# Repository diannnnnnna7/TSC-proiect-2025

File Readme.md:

E-Book Reader cu e-Paper si ESP32-C6

DeskAssistant este un dispozitiv portabil de tip E-Book Reader, construit in jurul microcontrolerului ESP32-C6, cu consum redus de energie si capabilitati de conectivitate Wi-Fi. Dispozitivul utilizeaza un display e-paper pentru citirea confortabila a cartilor, fiind alimentat de la o baterie Li-Po si gandit sa functioneze autonom timp indelungat.

Componente principale:

ESP32-C6 – Microcontroler principal cu Wi-Fi, SPI si I2C

E-Paper Display – Afisaj principal, ideal pentru citirea fara oboseala a ochilor

Memorie Flash NOR 64MB – Spatiu generos pentru carti, configurari sau fisiere

Senzor ambiental BME688 – Masoara temperatura, presiunea, umiditatea si calitatea aerului

RTC DS3231 – Ceas de timp real cu precizie ridicata si consum scazut

SD Card Slot – Optiune de stocare suplimentara pentru fisiere EPUB/PDF

Fuel Gauge MAX17048 – Monitorizeaza in timp real nivelul bateriei

LDO Regulator – Asigura tensiunea de 3.3V stabila pentru toate componentele

Conector USB-C – Incarcare si comunicatie UART pentru debugging

Dispozitivul se alimenteaza de la o baterie Li-Po si poate fi incarcat prin portul USB-C, avand un circuit de incarcare dedicat (MCP73831).

Interfete de comunicatie:

SPI – Utilizat pentru E-Paper, memorie Flash si card SD

I2C – Utilizat pentru senzorul BME688, RTC si Fuel Gauge

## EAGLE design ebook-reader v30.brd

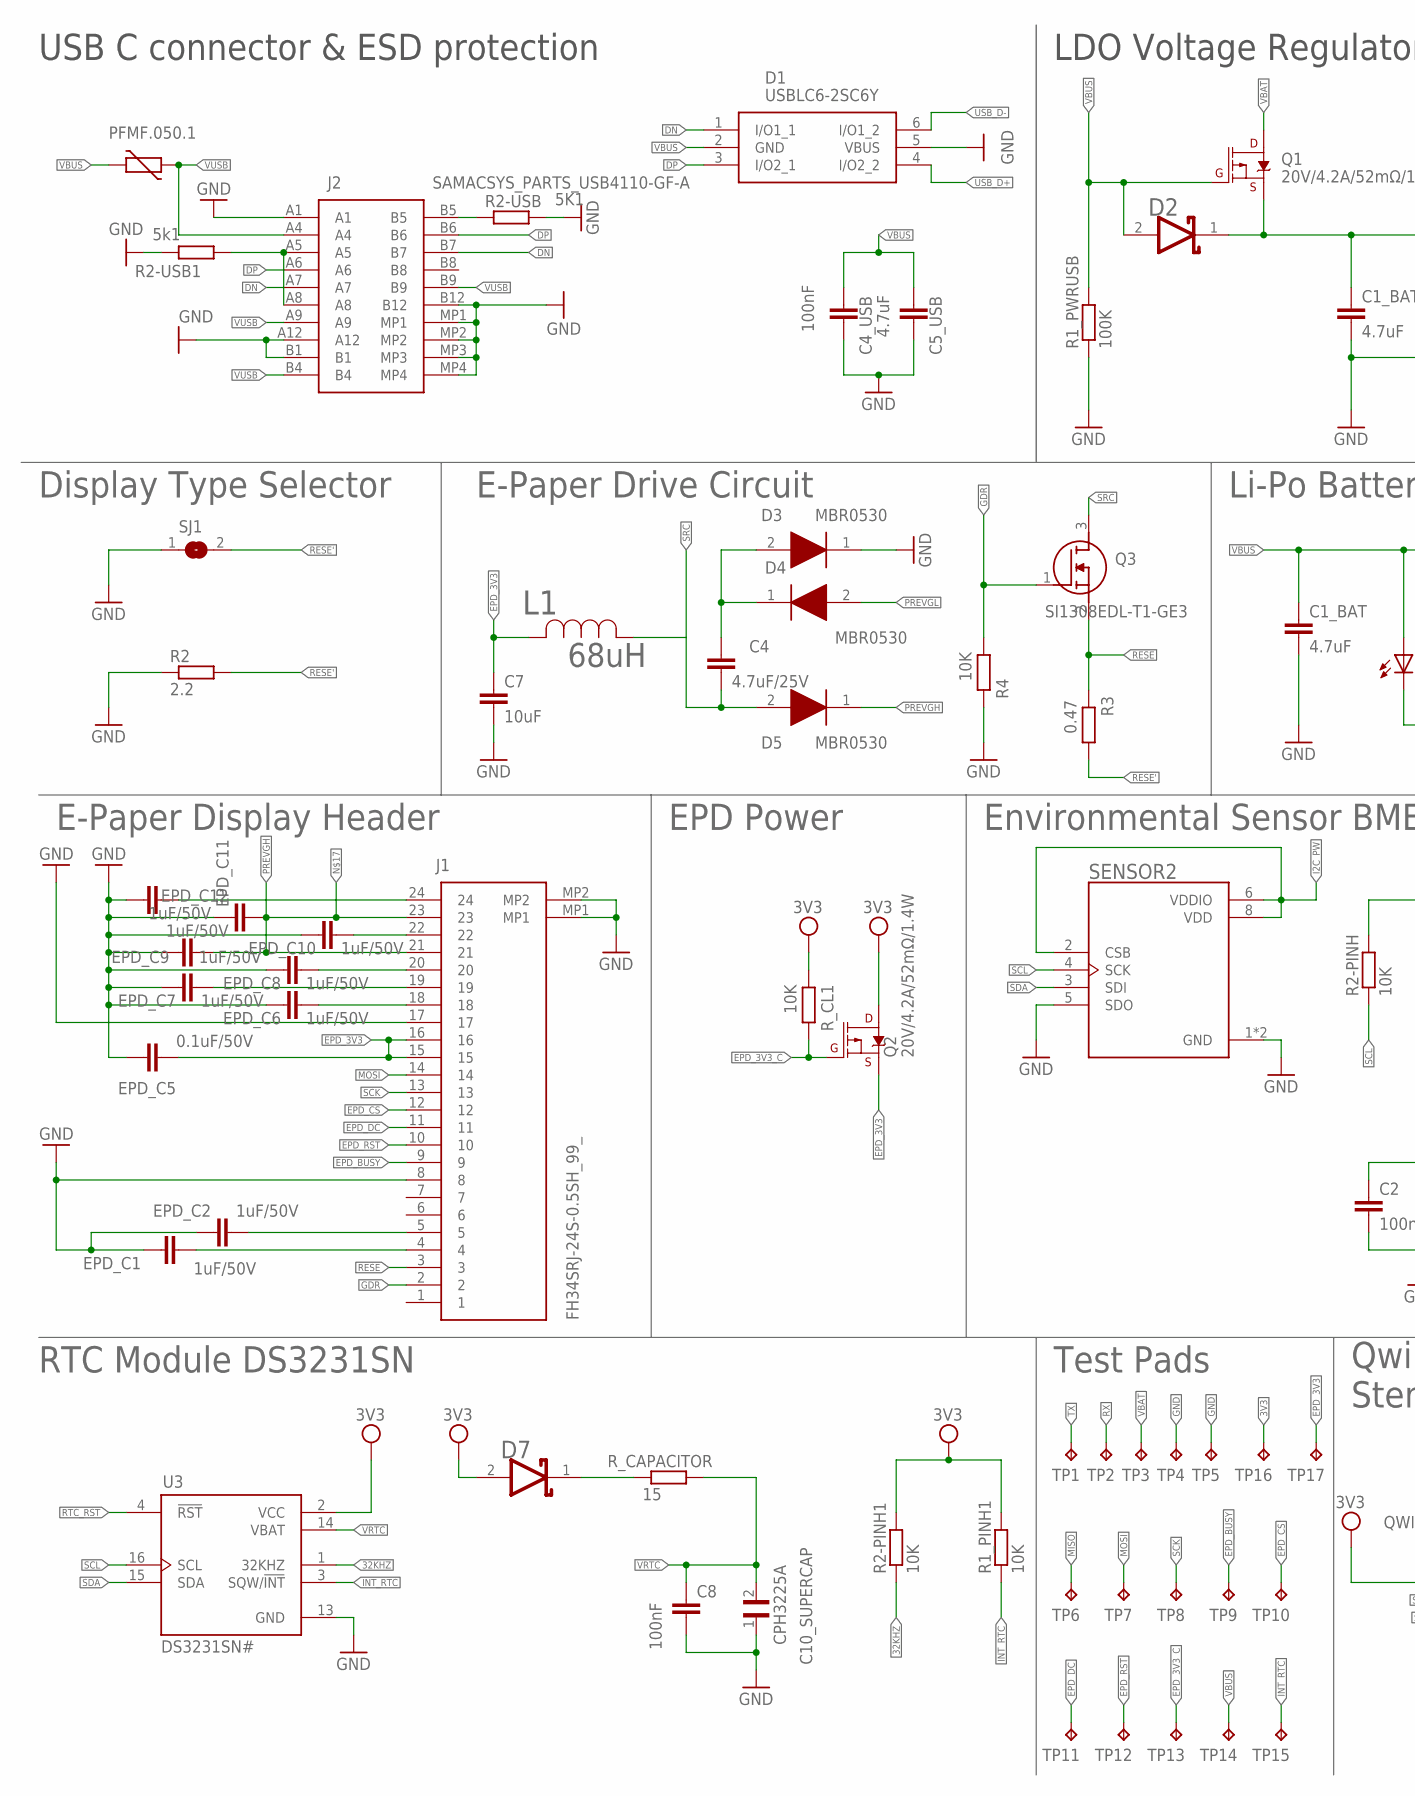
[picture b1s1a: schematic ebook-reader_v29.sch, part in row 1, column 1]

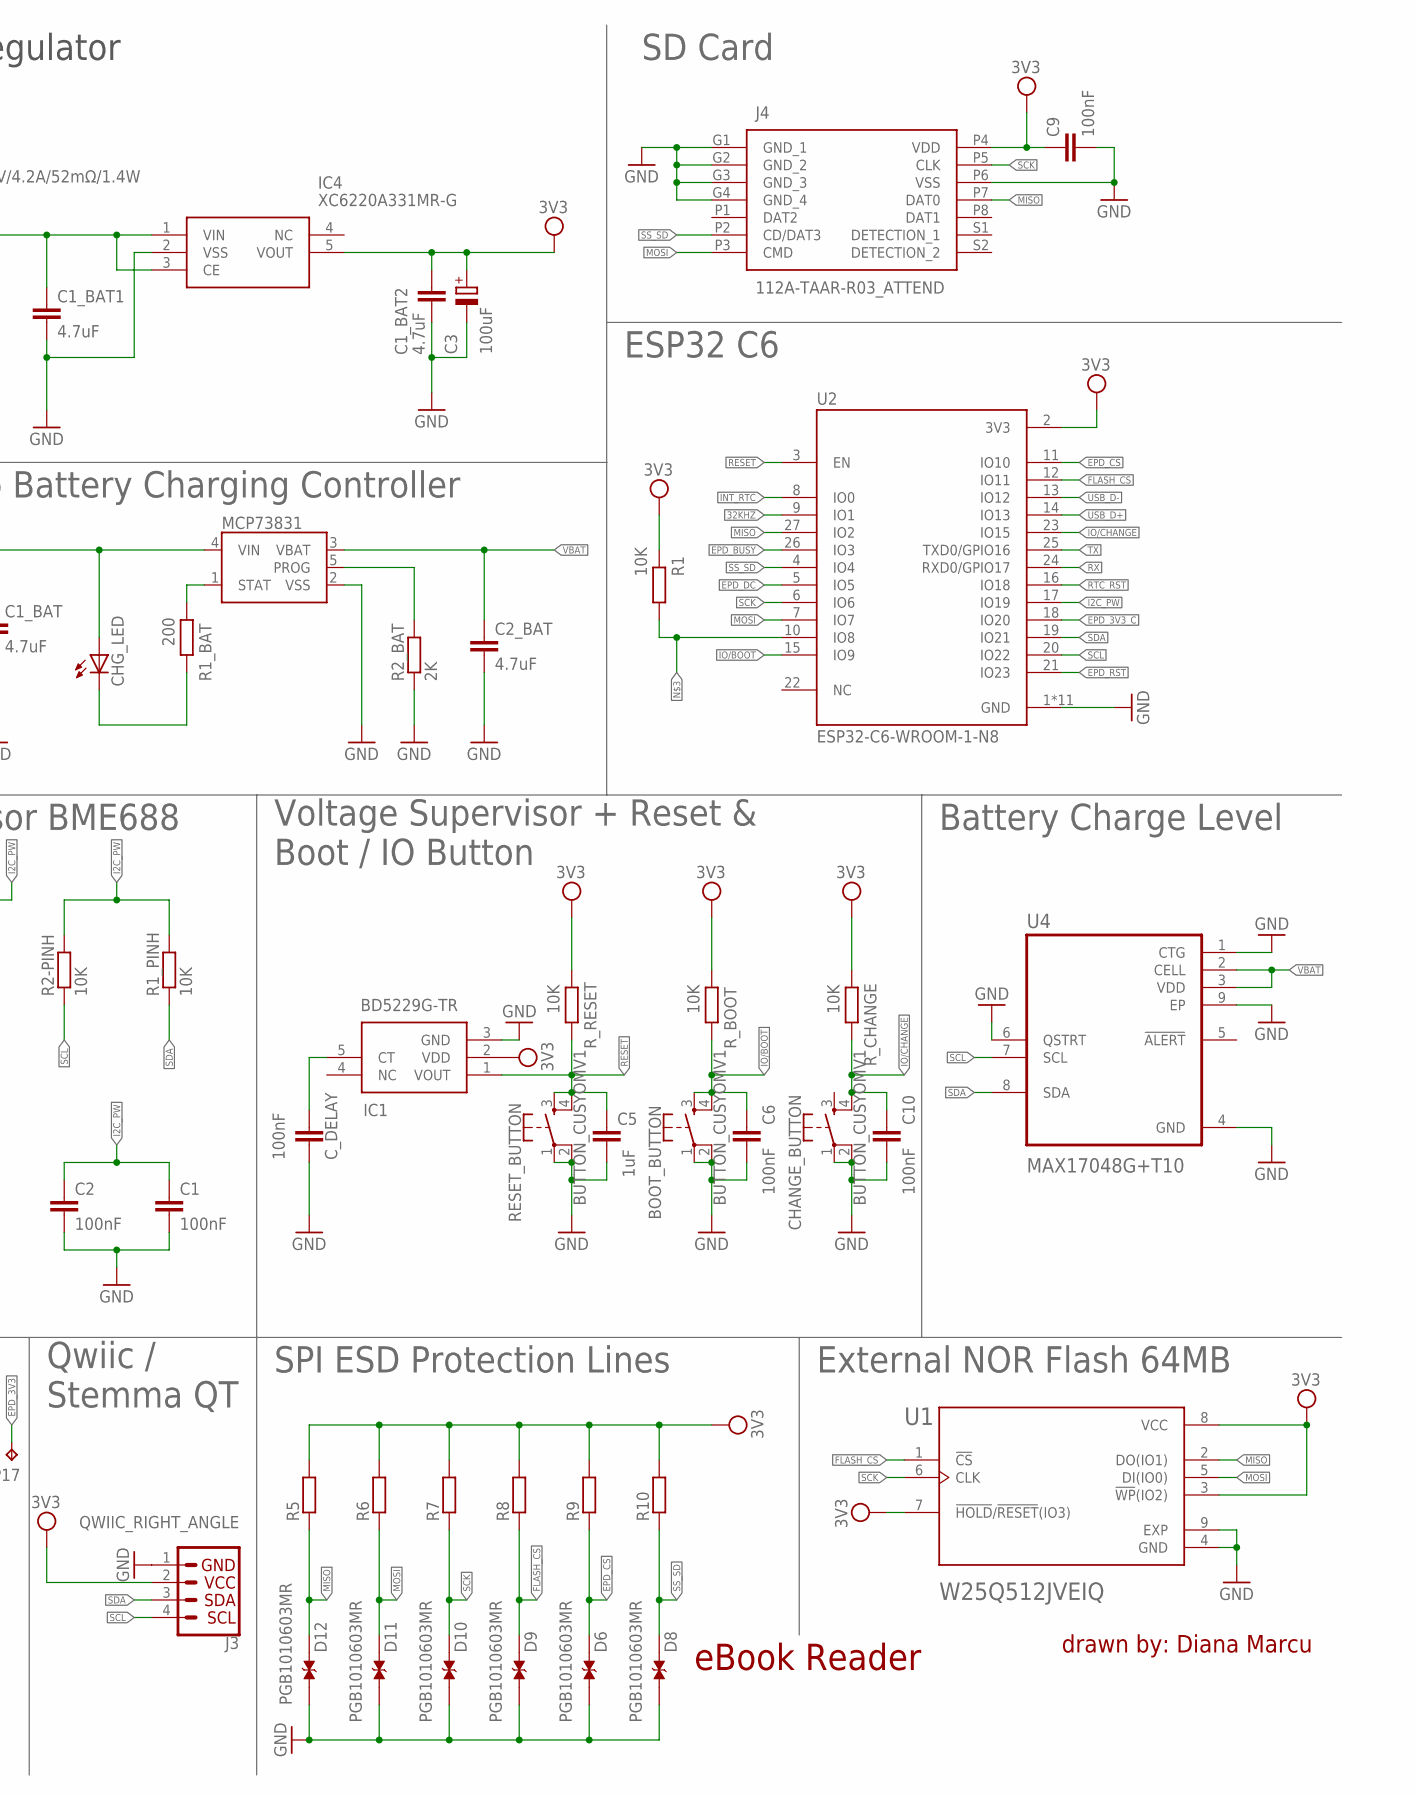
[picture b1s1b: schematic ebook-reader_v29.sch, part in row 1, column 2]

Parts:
BOOT_BUTTON: BUTTON_CUSYOMV1; MYBUTTON
C1, C2, C4_USB, C6, C8, C9, C10: 100nF; EAGLE-LTSPICE_C0402
C1_BAT, C1_BAT1, C1_BAT2, C2_BAT, C5_USB: 4.7uF; EAGLE-LTSPICE_C0402
C3: 100uF; RCL_CT3528
C4: 4.7uF/25V; EAGLE-LTSPICE_C0402
C5: 1uF; EAGLE-LTSPICE_C0402
C7: 10uF; EAGLE-LTSPICE_C0402
C10_SUPERCAP: CPH3225A; CAPCP3225X100N
CHANGE_BUTTON: BUTTON_CUSYOMV1; MYBUTTON
CHG_LED: ADAFRUIT_LEDCHIP-LED0603; ADAFRUIT_CHIP-LED0603
C_DELAY: 100nF; EAGLE-LTSPICE_C0402
D1: USBLC6-2SC6Y; SOT95P280X145-6N
D2, D7: ESP32_WROVER_AVX---SD0805S020S1R0_AVX_SD0805S020S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; ESP32_WROVER_AVX---SD0805S020S1R0_AVX_SD0805S020S1R0_0
D3, D4, D5: MBR0530; SOD3716X135N
D6, D8, D9, D10, D11, D12: PGB1010603MR; DIOC1608X36N
EPD_C1, EPD_C2, EPD_C6, EPD_C7, EPD_C8, EPD_C9, EPD_C10, EPD_C11, EPD_C12: 1uF/50V; EAGLE-LTSPICE_C0402
EPD_C5: 0.1uF/50V; EAGLE-LTSPICE_C0402
IC1: BD5229G-TR; SOT95P280X125-5N
IC4: XC6220A331MR-G; SOT95P280X120-5N
J1: FH34SRJ-24S-0.5SH_99_; FH34SRJ24S05SH99
J2: SAMACSYS_PARTS_USB4110-GF-A; SAMACSYS_PARTS_USB4110GFA
J3: QWIIC_RIGHT_ANGLE; JST04_1MM_RA
J4: 112A-TAAR-R03_ATTEND; 112ATAARR03ATTEND
L1: 68uH; IND_4828-WE-TPC_WRE
MCP73831: ESP32_WROVER_SPARKFUN-IC-POWER_MCP73831; ESP32_WROVER_SPARKFUN-IC-POWER_SOT23-5
PFMF.050.1: ESP32C6_VARISTORCN1812; ESP32C6_VARISTOR_CT/CN1812
Q1, Q2: 20V/4.2A/52mΩ/1.4W; ESP32_WROVER_SPARKFUN-DISCRETESEMI_SOT23-3
Q3: SI1308EDL-T1-GE3; SOT65P210X110-3N
R1, R1_PINH, R1_PINH1, R2-PINH, R2-PINH1, R4: 10K; ESP32_WROVER_EAGLE-LTSPICE_R0402
R1_BAT: 200; ESP32_WROVER_EAGLE-LTSPICE_R0402
R1_PWRUSB: 100K; ESP32_WROVER_EAGLE-LTSPICE_R0402
R2: 2.2; ESP32_WROVER_EAGLE-LTSPICE_R0402
R2-USB: 5K1; ESP32_WROVER_EAGLE-LTSPICE_R0402
R2-USB1: 5k1; ESP32_WROVER_EAGLE-LTSPICE_R0402
R2_BAT: 2K; ESP32_WROVER_EAGLE-LTSPICE_R0402
R3: 0.47; ESP32_WROVER_EAGLE-LTSPICE_R0402
R5, R6, R7, R8, R9, R10: ESP32_WROVER_EAGLE-LTSPICE_RR0402; ESP32_WROVER_EAGLE-LTSPICE_R0402
RESET_BUTTON: BUTTON_CUSYOMV1; MYBUTTON
R_BOOT: 10K; ESP32_WROVER_EAGLE-LTSPICE_R0402
R_CAPACITOR: 15; ESP32_WROVER_EAGLE-LTSPICE_R0402
R_CHANGE: 10K; ESP32_WROVER_EAGLE-LTSPICE_R0402
R_CL1: 10K; ESP32_WROVER_EAGLE-LTSPICE_R0402
R_RESET: 10K; ESP32_WROVER_EAGLE-LTSPICE_R0402
SENSOR2: ESP32_WROVER_BME680_BME680; ESP32_WROVER_BME680_PSON80P300X300X100-8N
SJ1: SJ
TP1, TP2, TP3, TP4, TP5, TP6, TP7, TP8, TP9, TP10, TP11, TP12, TP13, TP14, TP15, TP16, TP17: TPTP20R; TP20R
U1: W25Q512JVEIQ; SON127P600X800X80-9N
U2: ESP32-C6-WROOM-1-N8; XCVR_ESP32-C6-WROOM-1-N8
U3: DS3231SN#; SOIC127P1032X265-16N
U4: MAX17048G+T10; SON50P200X200X80-9N

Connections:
3V3: C1_BAT2.1, C3.+, C9.1, D7.2 (ANODE), IC1.2 (VDD), IC4.5 (VOUT), J3.2, J4.P4 (VDD), Q2.3 (D), R1.2, R1_PINH1.2, R2-PINH1.2, R5.2, R6.2, R7.2, R8.2, R9.2, R10.2, R_BOOT.2, R_CHANGE.2, R_CL1.2, R_RESET.2, TP16.TP, U1.3 (!WP!(IO2)), U1.7 (!HOLD!/!RESET!(IO3)), U1.8 (VCC), U2.2 (3V3), U3.2 (VCC)
32KHZ: R2-PINH1.1, U2.9 (IO1), U3.1 (32KHZ)
DN: D1.1 (I/O1_1), J2.A7, J2.B7
DP: D1.3 (I/O2_1), J2.A6, J2.B6
EPD_3V3: C7.1, EPD_C5.2, J1.15, J1.16, L1.2, Q2.2 (S), TP17.TP
EPD_3V3_C: Q2.1 (G), R_CL1.1, TP13.TP, U2.18 (IO20)
EPD_BUSY: J1.9, TP9.TP, U2.26 (IO3)
EPD_CS: D11.2, J1.12, R9.1, TP10.TP, U2.11 (IO10)
EPD_DC: J1.11, TP11.TP, U2.5 (IO5)
EPD_RST: J1.10, TP12.TP, U2.21 (IO23)
FLASH_CS: D10.2, R8.1, U1.1 (!CS), U2.12 (IO11)
GDR: J1.2, Q3.1 (G), R4.2
I2C_PW: C1.1, C2.1, R1_PINH.2, R2-PINH.2, SENSOR2.2 (CSB), SENSOR2.6 (VDDIO), SENSOR2.8 (VDD), U2.17 (IO19)
INT_RTC: R1_PINH1.1, TP15.TP, U2.8 (IO0), U3.3 (SQW/!INT)
IO/BOOT: BOOT_BUTTON.3, BOOT_BUTTON.4, C6.1, R_BOOT.1, U2.15 (IO9)
IO/CHANGE: C10.1, CHANGE_BUTTON.4, R_CHANGE.1, U2.23 (IO15)
MISO: D6.2, J4.P7 (DAT0), R5.1, TP6.TP, U1.2 (DO(IO1)), U2.27 (IO2)
MOSI: D9.2, J1.14, J4.P3 (CMD), R6.1, TP7.TP, U1.5 (DI(IO0)), U2.7 (IO7)
unnamed: J2.A5, J2.A8, R2-USB1.2
unnamed: J2.B5, R2-USB.1
unnamed: C1_BAT1.1, D2.1 (CATHODE), IC4.1 (VIN), IC4.3 (CE), Q1.2 (S)
unnamed: CHG_LED.C, R1_BAT.1
unnamed: C4.1, D3.2 (A), D4.1 (K)
unnamed: MCP73831.1 (STAT), R1_BAT.2
unnamed: MCP73831.5 (PROG), R2_BAT.2
unnamed: EPD_C1.2, J1.4
unnamed: EPD_C2.2, J1.5
unnamed: C_DELAY.1, IC1.5 (CT)
unnamed: D7.1 (CATHODE), R_CAPACITOR.1
unnamed: EPD_C12.2, J1.24
unnamed: EPD_C10.2, J1.22
unnamed: EPD_C9.1, EPD_C11.2, J1.21, J1.23
unnamed: EPD_C8.2, J1.20
unnamed: EPD_C7.2, J1.19
unnamed: EPD_C6.2, J1.18
PREVGH: D5.1 (K)
RESE: J1.3, Q3.2 (S), R3.2
RESE': R2.2, R3.1, SJ1.2
RESET: C5.1, IC1.1 (VOUT), RESET_BUTTON.3, RESET_BUTTON.4, R_RESET.1, U2.3 (EN)
RTC_RST: U2.16 (IO18), U3.4 (!RST)
RX: TP2.TP, U2.24 (RXD0/GPIO17)
SCK: D8.2, J1.13, J4.P5 (CLK), R7.1, TP8.TP, U1.6 (CLK), U2.6 (IO6)
SCL: J3.4, R2-PINH.1, SENSOR2.4 (SCK), U2.20 (IO22), U3.16 (SCL), U4.7 (SCL)
SDA: J3.3, R1_PINH.1, SENSOR2.3 (SDI), U2.19 (IO21), U3.15 (SDA), U4.8 (SDA)
SRC: C4.2, D5.2 (A), L1.1, Q3.3 (D)
SS_SD: D12.2, J4.P2 (CD/DAT3), R10.1, U2.4 (IO4)
TX: TP1.TP, U2.25 (TXD0/GPIO16)
USB_D+: D1.4 (I/O2_2), U2.14 (IO13)
USB_D-: D1.6 (I/O1_2), U2.13 (IO12)
VBAT: C2_BAT.1, D2.2 (ANODE), MCP73831.3 (VBAT), Q1.1 (G), R1_PWRUSB.2, TP3.TP, U4.2 (CELL), U4.3 (VDD)
VBUS: C1_BAT.1, C4_USB.1, C5_USB.1, CHG_LED.A, D1.2 (GND), MCP73831.4 (VIN), PFMF.050.1.2, TP14.TP
VRTC: C8.1, C10_SUPERCAP.2, R_CAPACITOR.2, U3.14 (VBAT)
VUSB: J2.A4, J2.A9, J2.B4, J2.B9, PFMF.050.1.1

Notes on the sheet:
USB C connector & ESD protection
LDO Voltage Regulator
SD Card
Display Type Selector
E-Paper Drive Circuit
Li-Po Battery Charging Controller
ESP32 C6
E-Paper Display Header
EPD Power
Environmental Sensor BME688
Voltage Supervisor + Reset & Boot / IO Button
Battery Charge Level
RTC Module DS3231SN
Test Pads
Qwiic / Stemma QT
SPI ESD Protection Lines
External NOR Flash 64MB
eBook Reader
drawn by: Diana Marcu

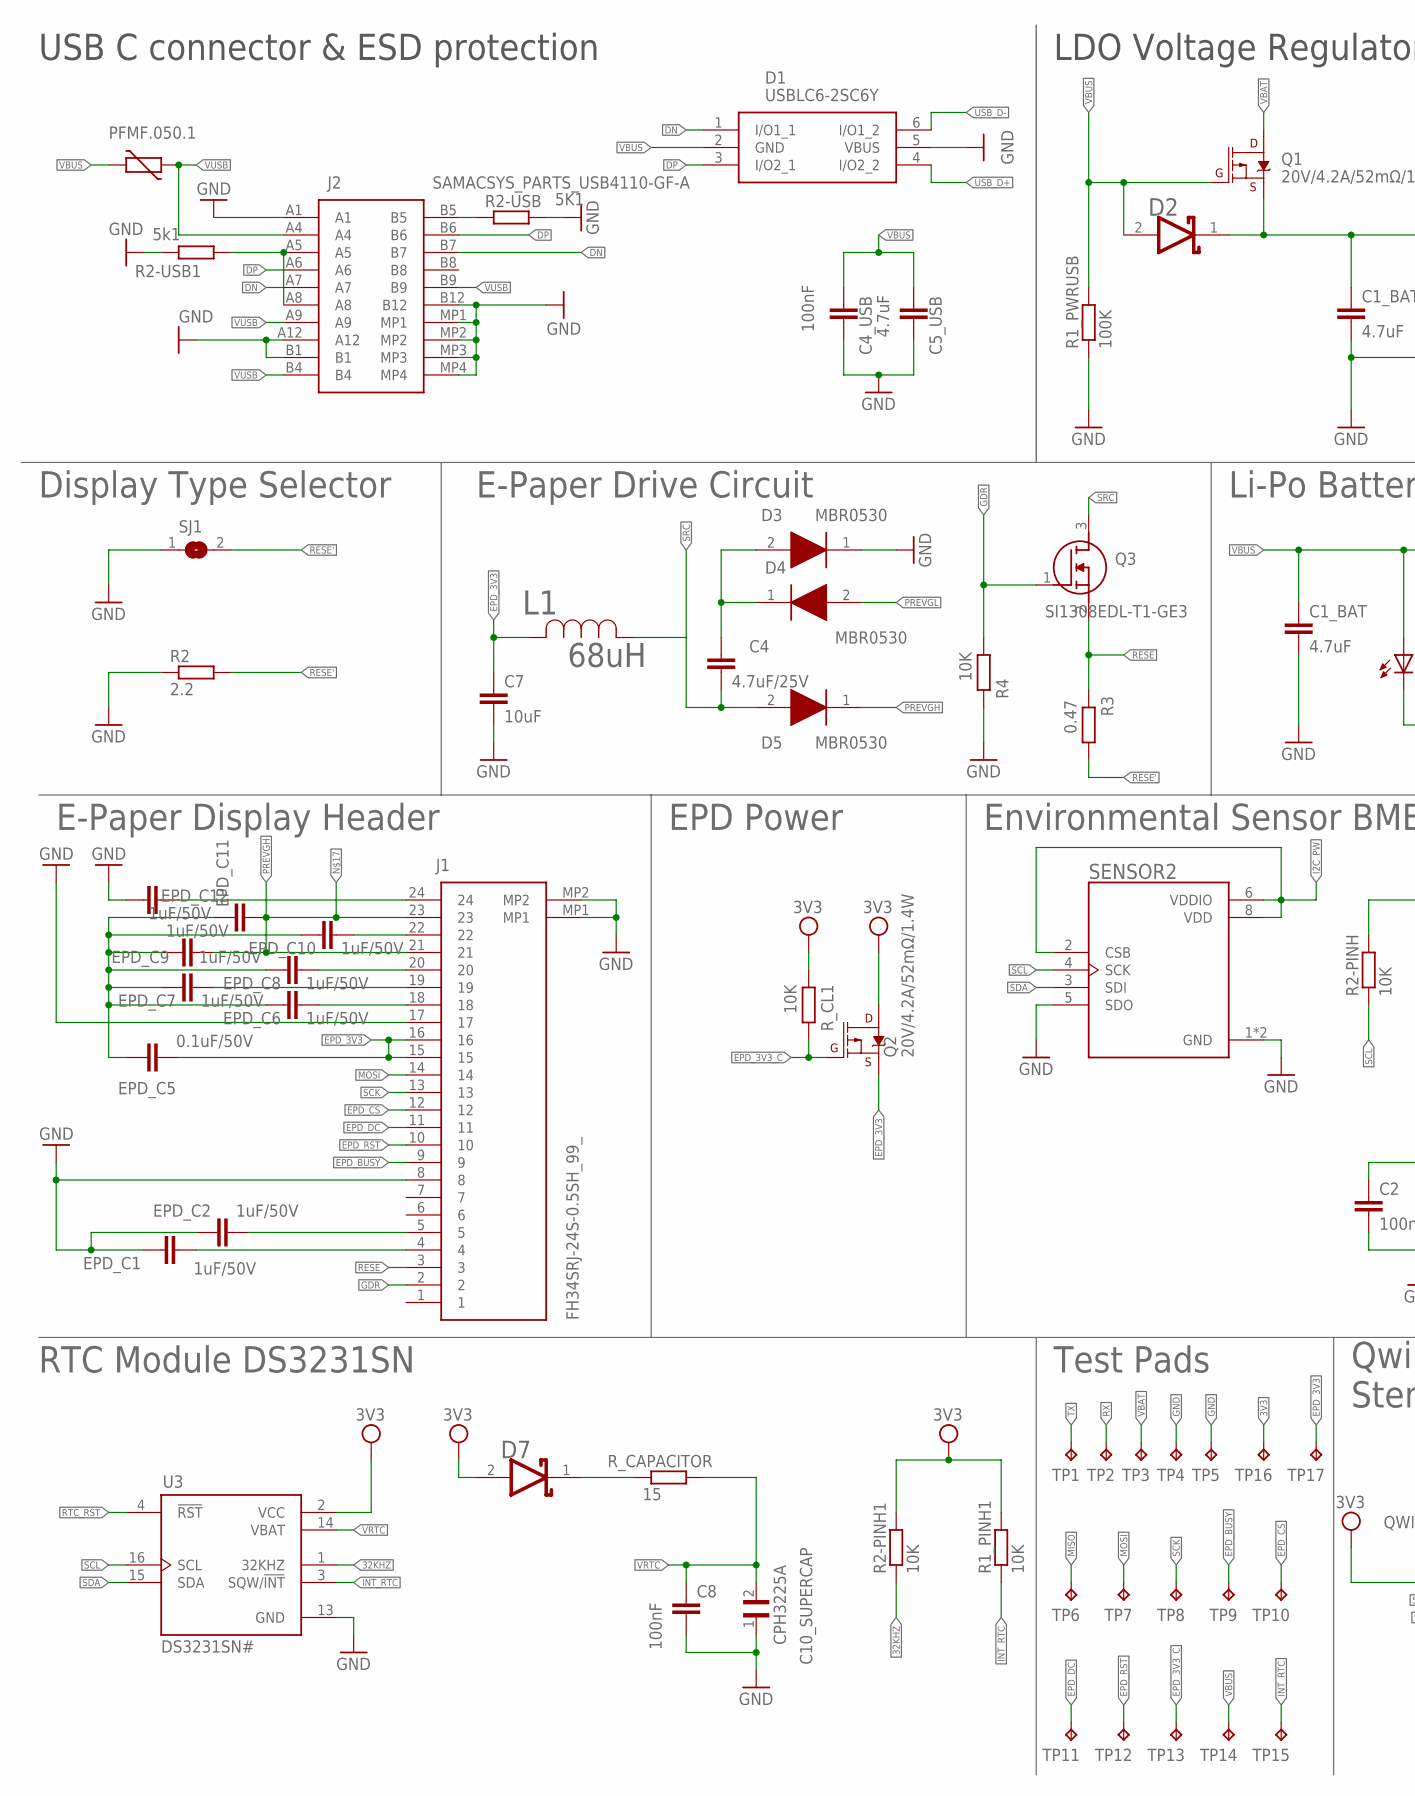
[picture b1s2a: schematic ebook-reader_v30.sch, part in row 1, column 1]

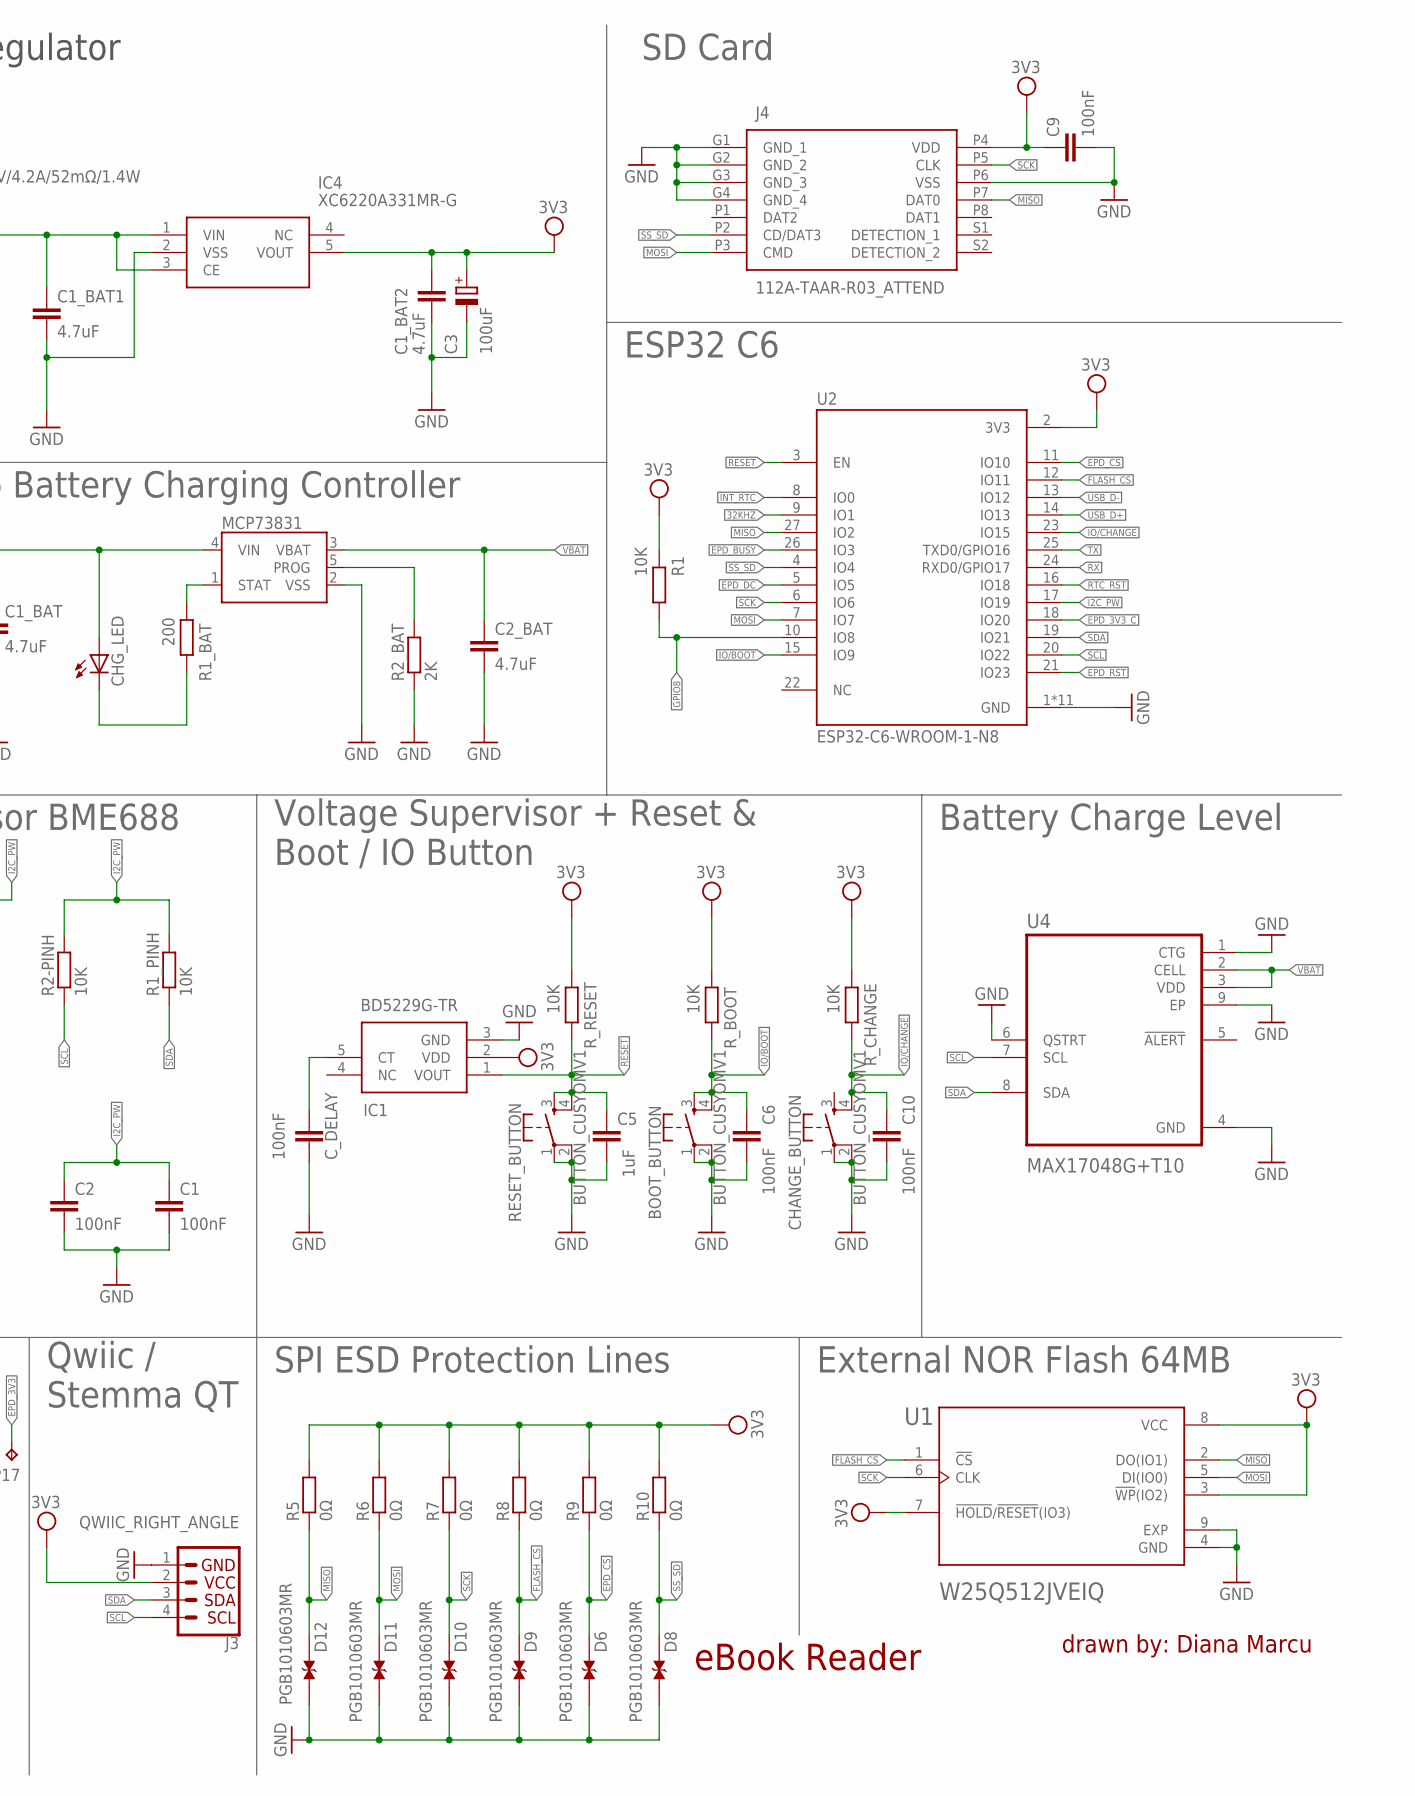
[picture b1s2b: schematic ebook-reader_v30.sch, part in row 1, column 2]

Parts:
BOOT_BUTTON: BUTTON_CUSYOMV1; MYBUTTON
C1, C2, C4_USB, C6, C8, C9, C10: 100nF; EAGLE-LTSPICE_C0402
C1_BAT, C1_BAT1, C1_BAT2, C2_BAT, C5_USB: 4.7uF; EAGLE-LTSPICE_C0402
C3: 100uF; RCL_CT3528
C4: 4.7uF/25V; EAGLE-LTSPICE_C0402
C5: 1uF; EAGLE-LTSPICE_C0402
C7: 10uF; EAGLE-LTSPICE_C0402
C10_SUPERCAP: CPH3225A; CAPCP3225X100N
CHANGE_BUTTON: BUTTON_CUSYOMV1; MYBUTTON
CHG_LED: ADAFRUIT_LEDCHIP-LED0603; ADAFRUIT_CHIP-LED0603
C_DELAY: 100nF; EAGLE-LTSPICE_C0402
D1: USBLC6-2SC6Y; SOT95P280X145-6N
D2, D7: ESP32_WROVER_AVX---SD0805S020S1R0_AVX_SD0805S020S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; ESP32_WROVER_AVX---SD0805S020S1R0_AVX_SD0805S020S1R0_0
D3, D4, D5: MBR0530; SOD3716X135N
D6, D8, D9, D10, D11, D12: PGB1010603MR; DIOC1608X36N
EPD_C1, EPD_C2, EPD_C6, EPD_C7, EPD_C8, EPD_C9, EPD_C10, EPD_C11, EPD_C12: 1uF/50V; EAGLE-LTSPICE_C0402
EPD_C5: 0.1uF/50V; EAGLE-LTSPICE_C0402
IC1: BD5229G-TR; SOT95P280X125-5N
IC4: XC6220A331MR-G; SOT95P280X120-5N
J1: FH34SRJ-24S-0.5SH_99_; FH34SRJ24S05SH99
J2: SAMACSYS_PARTS_USB4110-GF-A; SAMACSYS_PARTS_USB4110GFA
J3: QWIIC_RIGHT_ANGLE; JST04_1MM_RA
J4: 112A-TAAR-R03_ATTEND; 112ATAARR03ATTEND
L1: 68uH; IND_4828-WE-TPC_WRE
MCP73831: ESP32_WROVER_SPARKFUN-IC-POWER_MCP73831; ESP32_WROVER_SPARKFUN-IC-POWER_SOT23-5
PFMF.050.1: ESP32C6_VARISTORCN1812; ESP32C6_VARISTOR_CT/CN1812
Q1, Q2: 20V/4.2A/52mΩ/1.4W; ESP32_WROVER_SPARKFUN-DISCRETESEMI_SOT23-3
Q3: SI1308EDL-T1-GE3; SOT65P210X110-3N
R1, R1_PINH, R1_PINH1, R2-PINH, R2-PINH1, R4: 10K; ESP32_WROVER_EAGLE-LTSPICE_R0402
R1_BAT: 200; ESP32_WROVER_EAGLE-LTSPICE_R0402
R1_PWRUSB: 100K; ESP32_WROVER_EAGLE-LTSPICE_R0402
R2: 2.2; ESP32_WROVER_EAGLE-LTSPICE_R0402
R2-USB: 5K1; ESP32_WROVER_EAGLE-LTSPICE_R0402
R2-USB1: 5k1; ESP32_WROVER_EAGLE-LTSPICE_R0402
R2_BAT: 2K; ESP32_WROVER_EAGLE-LTSPICE_R0402
R3: 0.47; ESP32_WROVER_EAGLE-LTSPICE_R0402
R5, R6, R7, R8, R9, R10: 0Ω; ESP32_WROVER_EAGLE-LTSPICE_R0402
RESET_BUTTON: BUTTON_CUSYOMV1; MYBUTTON
R_BOOT: 10K; ESP32_WROVER_EAGLE-LTSPICE_R0402
R_CAPACITOR: 15; ESP32_WROVER_EAGLE-LTSPICE_R0402
R_CHANGE: 10K; ESP32_WROVER_EAGLE-LTSPICE_R0402
R_CL1: 10K; ESP32_WROVER_EAGLE-LTSPICE_R0402
R_RESET: 10K; ESP32_WROVER_EAGLE-LTSPICE_R0402
SENSOR2: ESP32_WROVER_BME680_BME680; ESP32_WROVER_BME680_PSON80P300X300X100-8N
SJ1: SJ
TP1, TP2, TP3, TP4, TP5, TP6, TP7, TP8, TP9, TP10, TP11, TP12, TP13, TP14, TP15, TP16, TP17: TPTP20R; TP20R
U1: W25Q512JVEIQ; SON127P600X800X80-9N
U2: ESP32-C6-WROOM-1-N8; XCVR_ESP32-C6-WROOM-1-N8
U3: DS3231SN#; SOIC127P1032X265-16N
U4: MAX17048G+T10; SON50P200X200X80-9N

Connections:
3V3: C1_BAT2.1, C3.+, C9.1, D7.2 (ANODE), IC1.2 (VDD), IC4.5 (VOUT), J3.2, J4.P4 (VDD), Q2.3 (D), R1.2, R1_PINH1.2, R2-PINH1.2, R5.2, R6.2, R7.2, R8.2, R9.2, R10.2, R_BOOT.2, R_CHANGE.2, R_CL1.2, R_RESET.2, TP16.TP, U1.3 (!WP!(IO2)), U1.7 (!HOLD!/!RESET!(IO3)), U1.8 (VCC), U2.2 (3V3), U3.2 (VCC)
32KHZ: R2-PINH1.1, U2.9 (IO1), U3.1 (32KHZ)
DN: D1.1 (I/O1_1), J2.A7, J2.B7
DP: D1.3 (I/O2_1), J2.A6, J2.B6
EPD_3V3: C7.1, EPD_C5.2, J1.15, J1.16, L1.2, Q2.2 (S), TP17.TP
EPD_3V3_C: Q2.1 (G), R_CL1.1, TP13.TP, U2.18 (IO20)
EPD_BUSY: J1.9, TP9.TP, U2.26 (IO3)
EPD_CS: D11.2, J1.12, R9.1, TP10.TP, U2.11 (IO10)
EPD_DC: J1.11, TP11.TP, U2.5 (IO5)
EPD_RST: J1.10, TP12.TP, U2.21 (IO23)
FLASH_CS: D10.2, R8.1, U1.1 (!CS), U2.12 (IO11)
GDR: J1.2, Q3.1 (G), R4.2
I2C_PW: C1.1, C2.1, R1_PINH.2, R2-PINH.2, SENSOR2.2 (CSB), SENSOR2.6 (VDDIO), SENSOR2.8 (VDD), U2.17 (IO19)
INT_RTC: R1_PINH1.1, TP15.TP, U2.8 (IO0), U3.3 (SQW/!INT)
IO/BOOT: BOOT_BUTTON.3, BOOT_BUTTON.4, C6.1, R_BOOT.1, U2.15 (IO9)
IO/CHANGE: C10.1, CHANGE_BUTTON.4, R_CHANGE.1, U2.23 (IO15)
MISO: D6.2, J4.P7 (DAT0), R5.1, TP6.TP, U1.2 (DO(IO1)), U2.27 (IO2)
MOSI: D9.2, J1.14, J4.P3 (CMD), R6.1, TP7.TP, U1.5 (DI(IO0)), U2.7 (IO7)
unnamed: J2.A5, J2.A8, R2-USB1.2
unnamed: J2.B5, R2-USB.1
unnamed: C1_BAT1.1, D2.1 (CATHODE), IC4.1 (VIN), IC4.3 (CE), Q1.2 (S)
unnamed: CHG_LED.C, R1_BAT.1
unnamed: C4.1, D3.2 (A), D4.1 (K)
unnamed: MCP73831.1 (STAT), R1_BAT.2
unnamed: MCP73831.5 (PROG), R2_BAT.2
unnamed: EPD_C1.2, J1.4
unnamed: EPD_C2.2, J1.5
unnamed: C_DELAY.1, IC1.5 (CT)
unnamed: D7.1 (CATHODE), R_CAPACITOR.1
unnamed: EPD_C12.2, J1.24
unnamed: EPD_C10.2, J1.22
unnamed: EPD_C9.1, EPD_C11.2, J1.21, J1.23
unnamed: EPD_C8.2, J1.20
unnamed: EPD_C7.2, J1.19
unnamed: EPD_C6.2, J1.18
PREVGH: D5.1 (K)
RESE: J1.3, Q3.2 (S), R3.2
RESE': R2.2, R3.1, SJ1.2
RESET: C5.1, IC1.1 (VOUT), RESET_BUTTON.3, RESET_BUTTON.4, R_RESET.1, U2.3 (EN)
RTC_RST: U2.16 (IO18), U3.4 (!RST)
RX: TP2.TP, U2.24 (RXD0/GPIO17)
SCK: D8.2, J1.13, J4.P5 (CLK), R7.1, TP8.TP, U1.6 (CLK), U2.6 (IO6)
SCL: J3.4, R2-PINH.1, SENSOR2.4 (SCK), U2.20 (IO22), U3.16 (SCL), U4.7 (SCL)
SDA: J3.3, R1_PINH.1, SENSOR2.3 (SDI), U2.19 (IO21), U3.15 (SDA), U4.8 (SDA)
SRC: C4.2, D5.2 (A), L1.1, Q3.3 (D)
SS_SD: D12.2, J4.P2 (CD/DAT3), R10.1, U2.4 (IO4)
TX: TP1.TP, U2.25 (TXD0/GPIO16)
USB_D+: D1.4 (I/O2_2), U2.14 (IO13)
USB_D-: D1.6 (I/O1_2), U2.13 (IO12)
VBAT: C2_BAT.1, D2.2 (ANODE), MCP73831.3 (VBAT), Q1.1 (G), R1_PWRUSB.2, TP3.TP, U4.2 (CELL), U4.3 (VDD)
VBUS: C1_BAT.1, C4_USB.1, C5_USB.1, CHG_LED.A, D1.2 (GND), MCP73831.4 (VIN), PFMF.050.1.2, TP14.TP
VRTC: C8.1, C10_SUPERCAP.2, R_CAPACITOR.2, U3.14 (VBAT)
VUSB: J2.A4, J2.A9, J2.B4, J2.B9, PFMF.050.1.1

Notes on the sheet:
USB C connector & ESD protection
LDO Voltage Regulator
SD Card
Display Type Selector
E-Paper Drive Circuit
Li-Po Battery Charging Controller
ESP32 C6
E-Paper Display Header
EPD Power
Environmental Sensor BME688
Voltage Supervisor + Reset & Boot / IO Button
Battery Charge Level
RTC Module DS3231SN
Test Pads
Qwiic / Stemma QT
SPI ESD Protection Lines
External NOR Flash 64MB
eBook Reader
drawn by: Diana Marcu

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
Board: 2 copper layers, 103 parts (0 on the bottom side), 55 nets, no tracks yet.

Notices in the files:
parts and their libraries:
COPYRIGHT: Copyright (C) 2024 Ultra Librarian. All rights reserved.
